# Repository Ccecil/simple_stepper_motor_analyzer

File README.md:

# Simple Stepper Motor Analyzer

Modifications made in this fork are largely due to parts shortages.  This allows the use of the TMCS1100A4-Q1 current sensor as an option.
Changes made:
&nbsp;
-Current sensor layout and traces
&nbsp;
-Added jumpers for switching 3.3/5v to the current sensors
&nbsp;
-Added voltage dividers to setup vref for the TMCS1100A4-Q1 (DNP if using default sensor)
&nbsp;
-Holes placed to orient the Stencil8 jig for ease of paste stenciling.
&nbsp;

<span style="color:red"><b>
NOTE (June 2021): The old design of the Simple Stepper Motor analyzer which was based on the STM32 was moved to https://github.com/zapta/legacy_stepper_motor_analyzer. This is a new and improve design that is based on the Raspberry Pi Pico and a 'bare' TFT panel.</b></span> 

&nbsp;

https://github.com/zapta/simple_stepper_motor_analyzer

&nbsp;

&nbsp;

&nbsp;

## Demonstration

Michael from the Teaching Tech youtube channel made [a great video explaining how stepper motors work](https://youtu.be/4iII25DGIdA) and used the Simple Stepper Motor Analyzer for some of the demonstrations. 

&nbsp;

## Highlights
* Low cost and minimalist DYI hardware design.
* Standalone. Doesn't require a computer to operate.
* Analyzes the stepper motor signals in the actual system (e.g. a 3D printer).
* Galvanically isolated current sensors. Does not interfere with the operating equipment, even when its turned off.
* Easy to connect using a pair 4 wire pass through connectors.
* Intuitive user interface with color display and a capacitive touch.
* Microstepping resolution of 1% of a full step.
* Provides momentary readings, signal patterns, and statistical measurements.
* Hardware and software are open sourced with a generous license.
* Based on free tools (Kicad, platformio, LVGL) and the Raspberry Pi Pico.
* Can be easily customized (new featured, cost reduction, data link to a computer, etc).
* Powered 5VDC, 200ma via a USB-C connector.

## Overview
Diagnosing the operation of stepper motor in 3D printers and CNC machines used to require stepper motor analyzers that costs thousands of dollar. Not anymore! The Simple Stepper Analyzer ('Analyzer' in short) brings these capabilities to every maker for a tiny fraction of the price and with a minimalist DIY electronic design that leaves the heavy lifting to the firmware.

The Analyzer is self contained, has two 4-wires pass-through connectors connecting the stepper motor, is powered from a common 5V charger with a micro USB cable, provides a simple to use graphical user interface with a 3.5" color touch screen, and provides a plethora of stepper motor measurements.

The Analyzer is provided to the community as a public domain reference design that can be built and used as is, or be customized with additional features or for a lower cost as desired. The hardware and firmware come with a liberal open source license (CC0) that allows commercial usages and doesn't require code source code sharing.

---
## Disclaimer
THE DESIGN IS PROVIDED "AS IS", WITHOUT WARRANTY OF ANY KIND, EXPRESS OR IMPLIED, INCLUDING BUT NOT LIMITED TO THE WARRANTIES OF MERCHANTABILITY, FITNESS FOR A PARTICULAR PURPOSE AND NONINFRINGEMENT. IN NO EVENT SHALL THE AUTHORS OR COPYRIGHT HOLDERS BE LIABLE FOR ANY CLAIM, DAMAGES OR OTHER LIABILITY, WHETHER IN AN ACTION OF CONTRACT, TORT OR OTHERWISE, ARISING FROM, OUT OF OR IN CONNECTION WITH THE DESIGN OR THE USE OR OTHER DEALINGS IN THE DESIGN.

---
## How does it work?
The principle of operation is very simple, and so is the hardware design. The stepper motor is connected via 4 wire pass-though connectors that allow the Analyzer to monitor the current through the stepper's coils. The Analyzer's user low impedance current sensors that are galvanically isolated such does not interfere with the operation of the 3D printer or other equipment it monitors. The Analyzer measures the coils currents 100k times a second and uses firmware that analyzes the data, extracts the desired measurements, and present them on the screen. For example, this is how an analysis of the distribution of distance by speed distribution looks like:

---
## Operation is simple and intuitive

1. Turn off power to the equipment (e.g. 3D printer).
2. Disconnect the 4 wires of the stepper motor and connect them through the Analyzer two pass through connectors.
3. Power the analyzer using a 5V charger and a micro USB cable.
4. Turn on the equipment and get the stepper going.
5. Use the Analyzer's screen to view the measurements you want.

**NOTE:** The two pass-through connectors of the Analyzer are symmetric and  each can act as an input or output. 

**CAUTION:** Always connect and disconnect stepper motors when their controller is not energized, to reduce the risk of damage to the controller due to high voltage spikes. The analyser itself is not subject to that risk since its uses galvanically isolated current sensors.

**NOTE:** The only requirement for proper wiring is that the two wires of one coil should go through pins pair 1,2 and the two wires of the other coil should go through pin pair 3,4. The Analyzer doesn't care about the +/- polarity of the wires in each pair, nor does it care which of the two pass-through connectors is on the controller side and which one is on the stepper side.

**TRIVIA:**: The pin-out and the connector type of the Analyzer follows the Duet3D conventions, except that is uses right angle connector to save space.

---
## The Home Page
The Home page is first page shown when the Analyzer is powered on. It provides summary information as well as access to the Settings page.

&nbsp;

#### Page Data

Field | Description
:------------ | :-------------
 COIL&nbsp;1 | Momentary coil 1 current in Amps.
 COIL&nbsp;2 | Momentary coil 2 current in Amps.
 ERRORS | The number of phase errors detected so far. Phase errors happens when the current patterns are so distorted that a forward/backward movement cannot be determined.
 POWER | Indicates if the stepper motor is currently energized. This is determined by the sum of currents in they two coils.
 IDLES | The number of times that stepper motor change status from energized to non energized.
 STEPS | The distance the stepper moved so far. Each full step forward increments this value by one and each full step backward decrements it by one. When the stepper motor is energized, the display also shows fractional steps in resolution of 1/100th of a full step.

HINT: The fractional step value cannot be reset because it is derived from the momentary currents in the two coils. Only the stepper motor driver can reset the fraction by positioning the stepper motor on an exact full step.

HINT: To swap forward/backward directions of the Analyzer use the Settings page. This does not affect the stepper motor itself.

&nbsp;
#### Page Actions

Action | Description
:------------: | :-------------
 | Clear all data.
 | Open the Settings page.

&nbsp;

---

## The Settings Page

This is a special page that is accessible from the Home page and allows to calibrate the Analyzer. The settings are stored in a non volatile memory and are preserved when the Analyzer is turned off.

&nbsp;
#### Page Data

Data | Description
:------------: | :-------------
COIL&nbsp;1 | The momentary current of stepper coil 1 in Amp units. Should be zero, or very close to zero, when the stepper motor is disconnected.
COIL&nbsp;2 | The momentary current of stepper coil 2 in Amp units. Should be zero, or very close to zero, when the stepper motor is disconnected.

&nbsp;
#### Page Actions

Action | Description
:------------: | :-------------
SET ZERO | Used to calibrate the zero reading of the current sensors. To do so, Disconnect the stepper motor and press this button.
REVERSE STEPS DIRECTION | Changes the forward/backward step directions of the Analyzer. Does not affect the stepper motor itself. Having the correct direction is important for measurements such as the Retraction analysis.
 | Press exist the Settings page.

&nbsp;

---

## The Speed Dial Page

This page measure the stepper speed in units of full steps per second. 

&nbsp;
#### Page Data

Data | Description
:------------ | :-------------
Speed&nbsp;Dial | The speed dial shows the momentary stepper speed in full steps per second units. Forward speed is on the right side and backward speed is on the left.
Speed&nbsp;Value | This field shows the speed in a numeric form. IT is updated less frequently than the dial to allow easy reading.

&nbsp;
**HINT:** The Settings page allows to swap the forward/backward directions.

&nbsp;
#### Page Actions

Action | Description
:------------: | :-------------
 | Clears all data.
Tap the dial |Toggles the dial's speed range.

&nbsp;

---

## The Distance Graph Page

This page shows scrolling graph with the total number of full steps vs. time.

&nbsp;

#### Page Data

Data | Description
:------------ | :-------------
Distance&nbsp;Graph | This graph shows how the distance, in units of full steps, changes over time.
Distance&nbsp;value | The numeric value of the distance in full steps.  This fields is identical to the STEPS field in the Home page.

&nbsp;

#### Page Actions

Action | Description
:------------: | :-------------
 | Clears all data.
Tap the graph | Toggles the range of the vertical axis.

&nbsp;

---

#### The Retraction Graph Page

This page is useful to analyze the retraction in of 3D printer extruder.

&nbsp;
**TRIVIA:** The graph above was taken while testing a direct extruder printer with [Thing #909901](https://www.thingiverse.com/thing:909901).
&nbsp;
#### Page Data

Data | Description
:------------ | :-------------
Retraction&nbsp;Graph | This graphs tracks the retraction of 3D extruder full step units.  Retraction is defined as the filament length that was inside the extruder and is now retracted outside of the extruder. 
Retraction value |  This field shows the current retraction level in a numeric form.

&nbsp;
#### Page Actions

Action | Description
:------------: | :-------------
 | Clear all data.
Tap the graph | Changes the range of the vertical axis.

&nbsp;

---

## The Time by Speed Page

This page shows an histogram with the distributing of time by stepper speed. That is how much time was spent in each speed range. The values are normalized such that the longest bar is always at 100%.

&nbsp;
#### Page Data

Data | Description
:------------ | :-------------
Time&nbsp;Histogram | The horizontal axis indicates speed in full steps per second units. The height of each bar indicate the time of all steps in that speed range, with the length of the longest bar normalized to 100%.

&nbsp;
#### Page Actions

Action | Description
:------------: | :-------------
 | Clear all data.

&nbsp;

---

## The Distance by Speed Page

This page shows an histogram with the the distribution of distance by stepper speed.

&nbsp;
#### Page Data

Data | Description
:------------ | :-------------
Distance&nbsp;Histogram |  The horizontal axis indicates speed in full steps per second units. The height of each bar indicate the distance or number of steps in that speed range, with the length of the longest bar normalized to 100%.

&nbsp;
#### Page Actions

Action | Description
:------------: | :-------------
 | Clear all data.

&nbsp;

---

## The Current by Speed Page

This page measures the ability of the stepper motor's controller to maintain peak current at high speeds.

The screenshot below shows a healthy system where the peak current is virtually flat across the speed range.

The screenshot below shows a system that is not capable to maintain peak current and starves the stepper motor at high speeds, resulting in poor torque and possible skipped steps.

&nbsp;
#### Page Data

Data | Description
:------------ | :-------------
Peak&nbsp;Current&nbsp;Histogram | The horizontal axis indicates speed in full steps per second units. The height of each bar indicates the average peak current in Amps of  steps that speed range. 

&nbsp;
#### Page Actions

Action | Description
:------------: | :-------------
 | Clear all data.

&nbsp;

---

## Coil Current Patterns Page

This page shows the current patterns in the two stepper coils.

The screenshot below shows a healthy system where the signals are nice and clean and reaches the target peak current.

&nbsp;

The screenshot below is from a poor system where high speed results in distorted and insufficient current, resulting in loss of torque and a potential for skipped steps.

&nbsp;

**GENERAL INFORMATION:** Each cycle of the stepper current pattern represent 4 full steps. The centers of those steps are at on the four vertical dotted lines where the currents of the two coils are identical, in the same or in  opposite polarities. The transitions between the steps are on the 4 vertical solid lines where one of the coils is at zero current. This cycle of 4 full steps is sometimes referred to as a single 'electric rotation'. The analyzer computes the exact phase on this cycle using the standard trigonometric function atan2(current1, current2) which can also be calculated manually from the current readings in the Home page.

&nbsp;

#### Page Data

Data | Description
:------------ | :-------------
Current&nbsp;graph | The horizontal axis indicates time in milliseconds. The vertical axis indicate coil current level in Amps. The two graphs show the current patterns of the respective stepper coils.

**NOTE:** The graph is updated only when sufficient stepper motor movement is detected.

&nbsp;
#### Page Actions

Action | Description
:------------: | :-------------
 | Clear all data.
 | When running, pauses the display updates.
 | When paused, resume the display updates.
Tap the graph | This toggles the range of the horizontal axis.

&nbsp;

---

## Coil Current Phase Page

This page draws the current patterns of the two coils as a [Lissajous curve](https://en.wikipedia.org/wiki/Lissajous_curve) which allows to examine visually distortions such as non sinusoidal current, phase distortion, and reduced amplitude.

In an ideal system, the graph is a perfect smooth circle, that doesn't change its size when the stepper's speed changes. Patterns that significantly diverge from that indicates a sub optimal configuration and operation.

Following picture shows a pattern from a well functioning system. The graph is round, reasonable smooth, and has sufficient size which indicates good current drive. 

The horizontal axis indicates the coil 1 current and the vertical axis indicates coil 2 current. In this example, both span nicely between -2A to +2A.

&nbsp;

The screenshot below is from a poor system where high speed results in distorted and insufficient current, resulting in loss of torque and a potential for skipped steps. The pattern is far from a clean circle and the shape has reduced size.

&nbsp;

The screenshot below shows a sub optimal operation where a a speed increase of the stepper results in small (less current and torque) and even more distorted curve.

&nbsp;

The screenshot below shows a well functioning system. The smaller size of the circle compare to the example above indicates that it operates on lower current.

&nbsp;

The screenshot below show an operation of a stepper in full steps mode. The dimension of the pattern indicate good current feed, and the square  shape is the best a full step driver can deliver.

&nbsp;

The screenshot below show an operation of a stepper in half steps mode. The dimension of the pattern indicate good current feed, and the shape is somewhere between the square shape of full step mode and the round shape of micro stepping interpolation mode.

&nbsp;

#### Page Data

Data | Description
:------------ | :-------------
Lissajous&nbsp;curve | A Lissajous curve drawn from the current pattern of coil 1 (x) and coil2(y). 
Capture speed | Shows the signal capture time. Fast mode works better with fast moving steppers and slow mode works with slow moving steppers. Tap the graph to toggle.

**NOTES** 
* The graph is updated only when sufficient stepper motor movement is detected.
* To view the current pattern that resulted in the current phase pattern, use the navigation button to switch the current patters page, and vice versa.

&nbsp;
#### Page Actions

Action | Description
:------------: | :-------------
 | Clear all data.
 | When running, pauses the display updates.
 | When paused, resume the display updates.
Tap the graph | This toggles the capture time between fast and slow speeds.

&nbsp;

---

## Reference Design Specification

Item | Specification
:------------ | :------------- 
Power consumption | 5V, 175ma.
Power connector | micro USB
MCU | Raspberry Pi RP2040 (Pico module).
Flashing | Drag and drop to a virtual disk.
Data link | USB/Serial link available but not used.
Current measurement | +/-2.5A per coil. (+/-5A sensors optional).
PCB | 102mm x 57mm, two layers
Enclosure | 3D printed, 108.4mm x 63.4mm x 16.6mm
Display | 3.5" 480 x 320, Color, Landscape mode.
Touch screen | Capacitive
Sensor isolation | See ACS70331 data sheet
Sampling rate | 100Khz per channel.
Sampling resolution | 12bits
Current accuracy | estimated at +/- 1%
Max step rate | Software dependent. Currently 2K full steps/sec.
Step resolution | 1/100th of a full step.
User settings storage | On board FLASH.
GUI framework | LVGL library. R3G3B2 color depth.
Programming language | C++
Programming IDE | VSCode, Platformio, WizIO.
Electronic design software | Kicad.
Mechanical design software | Onshape. 

&nbsp;

---

## I want to build me one

The electronic schematic, PCB layout, gerber files, and the firmware source files and released binary are all available on this github repository.

[Schematic](./kicad/stepper_analyzer.pdf)

[Production files](./kicad/JLCPCB)

[BOM](./kicad/BOM.xlsx)

&nbsp;

**Instructions:** Order the PCB with JLCPB with SMD service (see JLCPCB directory with gerbers and bom and pos files). Attach the Pico with XFasten tape and solder. Cut the bottom pins of the KF2510 connectors to 1mm length and solder from the top of the PCB only. Solder the current sensors, attach the TFT to the back of the PCB with XFasten tape and carefully connect the two FPC cables. Program the Pico by connecting it to a computer while it's bootsel button is pressed and drag he uf2 release file to the virtual disk you will see on your computer.

Note: The two servo connectors may be hard to insert and remove due to a small bump on the male side that is intended to lock in place the female connector. If you are handy with X-Acto knife, you can try carefully scraping that bump for easier insertion as I did (knives are sharp and may be dangarous, use proper precautions). 

&nbsp;

&nbsp;

&nbsp;

&nbsp;

## Mechanical
3D print the two part of the enclosure (STL files in this github repository), insert the four M2.5x3.5x3 heated inserts with a solder iron, drill the four  2.5 holes in the cover, insert the PCB to the front part, make sure the TFT seats flush with front and secure the back with four M2.5x10 hex cup screws.

## Ideas for improvements
The Analyzer is provided as a fully functional reference design and changes and the developers encourage improvement/modifications of the hardware and/or firmware are encouraged. This can include new features, new measurements and pages, extending the design to support 2 or 3 steppers at once to track the x/y/z of a 3D printer, reducing the hardware cost using less expensive screen TFT, or even eliminating the screen altogether and using the Analyzer as a dongle tethered to a computer via the existing USB/Serial link.

&nbsp;

---

## FAQ

#### Q: Can I buy from you a few units?

A: We cannot provide assembled units for the general public. For that reason, we released the design with CC Zero license with the hope that other entrepreneurs will do so.

#### Q: Where do you source the TFT panels?

A: We buy the '3.5 LCD CTP' variant here https://www.aliexpress.com/item/32862869103.html. The choice of TFT panel and the mechanical design of the PCB follows Dustin Watts' ESP32 Touchdown project https://www.tindie.com/products/dustinwattsnl/esp32-touchdown/ (with extra 2mm to the PCB's length for extra clearance for the threaded heat inserts).

#### Q: Can the firmware of the analyzer be updated?

A: Yes. New firmware is released as .uf2 files. To flash the analyzer with a compatible .uf2 follow the standard procedure of the Raspberry Pi Pico. Access to the BOTSEL button is provided by a hole at the back of the 3D printed enclosure.

#### Q: Why some footprints on the PCB are not populated?

A: The PCB design includes circuitry that helps developing firmware for the analyzer that is not necessary or helpful for normal opeation of the analyzer.

#### Q: Can the current scale of the two channels increased from +/-2.5A?

A: The PCB was designed to accept also +/-5A variants of the current sensors and the optionals resistors R8 R9 were added to allow configuring the firmware to know about the larger current scale. This however was not tried yet since most 3D printer steppers do not exceed currents of 2.5A.

#### Q: Why not a SPI based TFT?

A: We could not achieve fast enough display refresh rate with SPI so switched to 16 bit parallel data transfers. With the optimized firmware we can update rate equivalent to 200Mhz SPI. 

#### Q: Can a cheaper TFT/touch be used?
A: Yes, but it will require design changes.

#### Q: Can the TFT screen be eliminated?
A: Yes. The Analyzer has a USB/Serial output can a small Analyzer dongle can communicate with a computer program. This will require firmware changes.

#### Q: Can you add feature X or customization Y?

A: Most likely not. The reference design is provided for the community to change and mix.

#### Q: I want to commercialize or crowd source it, can you help me?

A: Not really. The reference design is open source and you will need to find others to help you. We don't mind though to answer questions.

#### Q: Where do I file a bug?

A: Use the github repository.

#### Q: Is it ok to connect/disconnect power to the Analyzer while my 3D printer prints?

A: Of course. The Analyzer is isolated from the stepper wires and should not interfere with the operation of the printer.

#### Q: The Analyzer uses LVGL lib, what is the license of that library?

A: At the time of writing this, the LVGL license is available here https://github.com/lvgl/lvgl/blob/master/LICENCE.txt.  The Analyzer's developers are not affiliated with LVGL.

#### Q: Is the LVGL library included in the Analyzer's repository?

A: It's not needed. LVGL is supported by platform.io so the Analyzer's project is set for platform.io to fetch LVGL automatically.

#### Q: Can the firmware be built with the standard Raspberry Pi Pico C++ SDK?

A: It should be but we didn't try it. Installing the SDK, libraries and tools using platformio and the WizIO Pico 'baremetal' distribution is easier.

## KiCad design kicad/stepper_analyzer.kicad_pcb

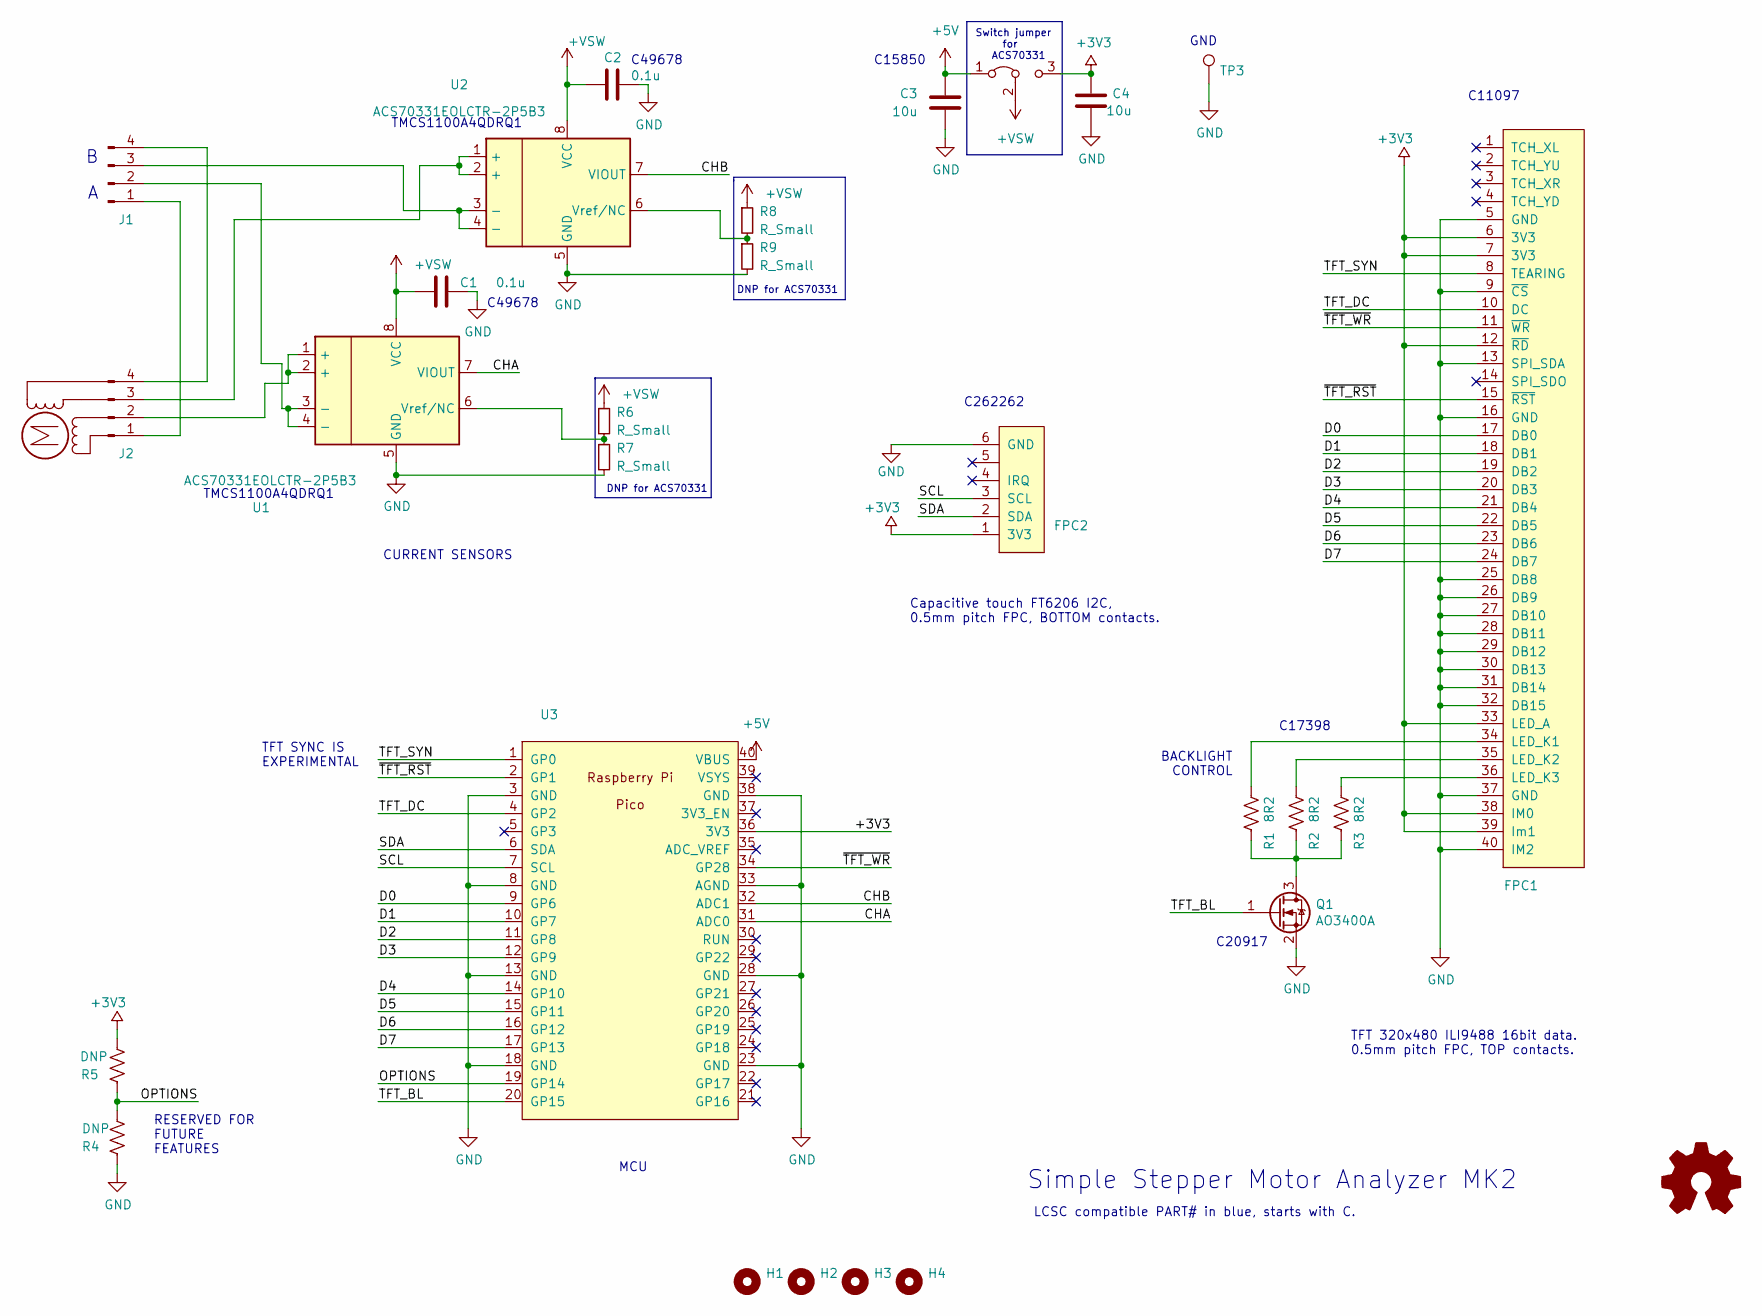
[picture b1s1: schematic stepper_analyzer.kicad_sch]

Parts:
C1, C2: 0.1u; C_0805_2012Metric_Pad1.15x1.40mm_HandSolder; LCSC C49678
C3, C4: 10u; C_0805_2012Metric_Pad1.15x1.40mm_HandSolder; LCSC C15850
FPC1: Connector_Conn_01x40_Female; JUSHUO-AFC07-S40ECC-00_40P_05mm_flipped; LCSC C11097
FPC2: FPC connector, 6 pins, 0.5mm, BOTTOM contacts; JUSHUO-AFC01-S06FCC-00_6p_05mm; LCSC C262262
H1, H2, H3, H4: MountingHole; MountingHole_2.5mm_Pad_Via
J1, J2: Connector_Conn_01x04_Male; connector_4pins_horizontal
JP1: Jumper_3_Bridged12; SolderJumper-3_P1.3mm_Open_RoundedPad1.0x1.5mm
LOGO1: Logo_Open_Hardware_Small; OSHW-Logo2_9.8x8mm_SilkScreen
M1: Motor; null_footprint
Q1: AO3400A; SOT-23; LCSC C20917
R1, R2, R3: 8R2; R_0805_2012Metric_Pad1.15x1.40mm_HandSolder; LCSC C25330
R4, R5: DNP; R_0805_2012Metric_Pad1.15x1.40mm_HandSolder_no_3d
R6, R7, R8, R9: R_Small; R_0402_1005Metric
TP3: TestPoint; testpoint_double_side
U1, U2: ACS70331EOLCTR-2P5B3; SOIC-8_3.9x4.9mm_P1.27mm
U3: Pico; Pico_smd_dedicated

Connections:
+3V3: C4.2, FPC1.6 (3V3), FPC1.7 (3V3), FPC1.12 (~RD), FPC1.33 (LED_A), FPC1.38 (IM0), FPC1.39 (Im1), FPC2.1 (3V3), JP1.3 (B), R5.2, U3.36 (3V3)
+5V: C3.2, JP1.1 (A), U3.40 (VBUS)
+VSW: C1.2, C2.2, JP1.2 (C), R6.1, R8.1, U1.8 (VCC), U2.8 (VCC)
/CHA: U1.7 (VIOUT), U3.31 (ADC0)
/CHB: U2.7 (VIOUT), U3.32 (ADC1)
/D0: FPC1.17 (DB0), U3.9 (GP6)
/D1: FPC1.18 (DB1), U3.10 (GP7)
/D2: FPC1.19 (DB2), U3.11 (GP8)
/D3: FPC1.20 (DB3), U3.12 (GP9)
/D4: FPC1.21 (DB4), U3.14 (GP10)
/D5: FPC1.22 (DB5), U3.15 (GP11)
/D6: FPC1.23 (DB6), U3.16 (GP12)
/D7: FPC1.24 (DB7), U3.17 (GP13)
/OPTIONS: R4.1, R5.1, U3.19 (GP14)
/SCL: FPC2.3 (SCL), U3.7 (SCL)
/SDA: FPC2.2 (SDA), U3.6 (SDA)
/TFT_BL: Q1.1 (G), U3.20 (GP15)
/TFT_DC: FPC1.10 (DC), U3.4 (GP2)
/TFT_SYN: FPC1.8 (TEARING), U3.1 (GP0)
/~TFT_RST: FPC1.15 (~RST), U3.2 (GP1)
/~TFT_WR: FPC1.11 (~WR), U3.34 (GP28)
GND: C1.1, C2.1, C3.1, C4.1, FPC1.5 (GND), FPC1.9 (~CS), FPC1.13 (SPI_SDA), FPC1.16 (GND), FPC1.25 (DB8), FPC1.26 (DB9), FPC1.27 (DB10), FPC1.28 (DB11), FPC1.29 (DB12), FPC1.30 (DB13), FPC1.31 (DB14), FPC1.32 (DB15), FPC1.37 (GND), FPC1.40 (IM2), FPC2.6 (GND), Q1.2 (S), R4.2, R7.2, R9.2, TP3.1, U1.5 (GND), U2.5 (GND), U3.3 (GND), U3.8 (GND), U3.13 (GND), U3.18 (GND), U3.23 (GND), U3.28 (GND), U3.33 (AGND), U3.38 (GND)
unnamed: FPC1.34 (LED_K1), R1.2
unnamed: FPC1.35 (LED_K2), R2.2
unnamed: FPC1.36 (LED_K3), R3.2
unnamed: J1.1, J2.1
unnamed: J1.2, U1.3 (-), U1.4 (-)
unnamed: J1.3, U2.3 (-), U2.4 (-)
unnamed: J1.4, J2.4
unnamed: J2.2, U1.1 (+), U1.2 (+)
unnamed: J2.3, U2.1 (+), U2.2 (+)
unnamed: Q1.3 (D), R1.1, R2.1, R3.1
unnamed: R8.2, R9.1, U2.6 (Vref/NC)
unnamed: R6.2, R7.1, U1.6 (Vref/NC)

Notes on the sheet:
CURRENT SENSORS
DNP for ACS70331
Switch jumper for ACS70331
TMCS1100A4QDRQ1
Simple Stepper Motor Analyzer MK2
TFT 320x480 ILI9488 16bit data. 0.5mm pitch FPC, TOP contacts.
RESERVED FOR FUTURE FEATURES
LCSC compatible PART# in blue, starts with C.
C17398
MCU
TFT SYNC IS EXPERIMENTAL
GND
Capacitive touch FT6206 I2C, 0.5mm pitch FPC, BOTTOM contacts.
C20917
C49678
C15850
C11097
C262262
BACKLIGHT CONTROL

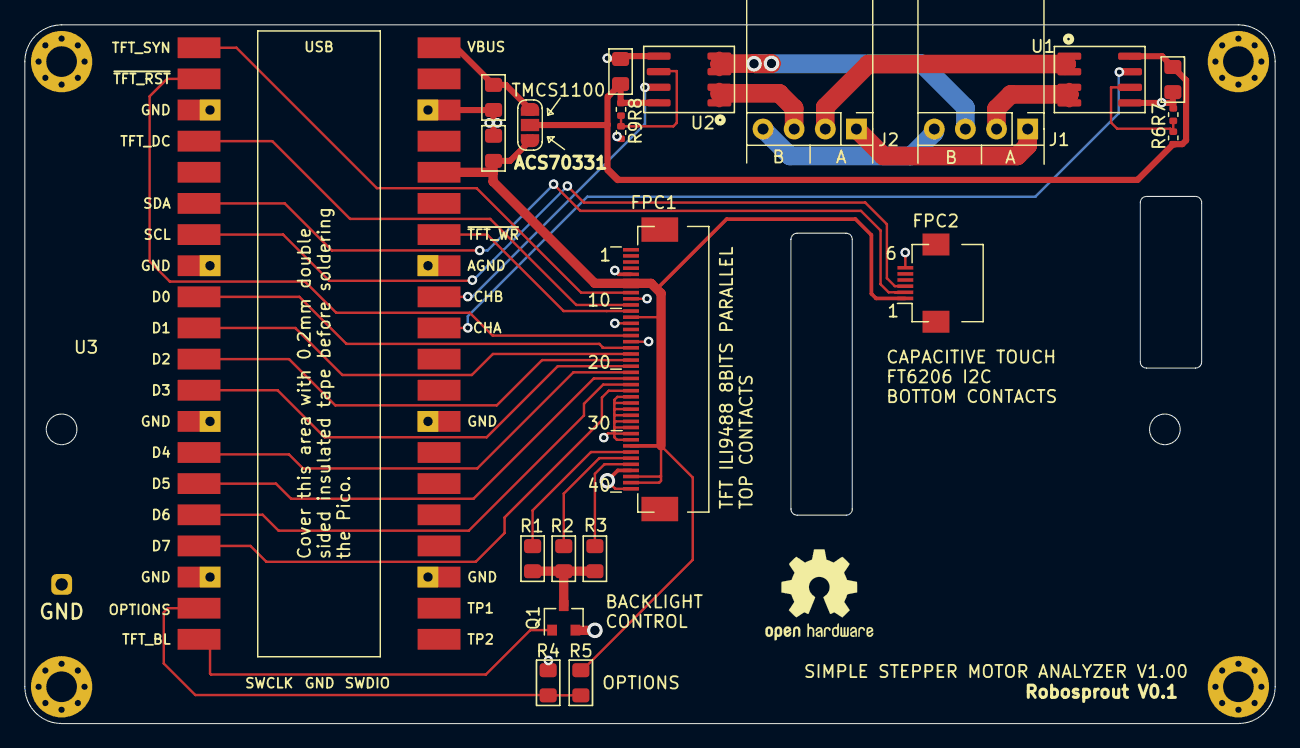
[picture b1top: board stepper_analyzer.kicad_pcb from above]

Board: 2 copper layers, 102.0 x 57.0 mm, 29 parts (1 on the bottom side), 34 nets.

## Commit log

2022-02-21 Added TMCS1100A4-Q1
    added TMCS1100A4-Q1 , voltage divider for vref, jumper option for 3.3/5v, stencil8 orientation holes

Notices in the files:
README.md:
Q: The Analyzer uses LVGL lib, what is the license of that library?:
A: At the time of writing this, the LVGL license is available here https://github.com/lvgl/lvgl/blob/master/LICENCE.txt.  The Analyzer's developers are not affiliated with LVGL.
